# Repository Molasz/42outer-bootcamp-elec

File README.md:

# Bootcamp Electronics - 42 Paris

_This project has been created as part of the 42 curriculum by molasz-a._

> Part of [42 Barcelona — molasz-a](https://github.com/Molasz/42), a monorepo centralizing every project completed at 42 Barcelona.

## Description

This repository contains the schematic, PCB layout and custom symbol and footprint for each component for a custom-designed microcontroller board based on the **ATmega328P**. The board was designed using KiCad 9.0.

## Bill of Materials (BOM)

| Reference | Qty | Name | Footprint | Description |
| :--- | :---: | :--- | :--- | :--- |
| **U1** | 1 | ATmega328P-AU | TQFP-32_7x7mm_P0.8mm | 8-bit AVR Microcontroller |
| **Y1** | 1 | 16.000 MHz | Crystal_SMD_3225-4Pin | SMD Quartz Crystal (3.2x2.5mm) |
| **C1, C2** | 2 | 12pF | C_0805_2012Metric | Ceramic Load Capacitors for Y1 |
| **C3, C4, C7**| 3 | 100nF | C_0805_2012Metric | Decoupling & DTR Capacitors |
| **C6**| 1 | 1uF | C_0805_2012Metric | Decoupling |
| **R1** | 1 | 330Ω | R_0805_2012Metric | Current limiting resistor for D1 |
| **R2, R3** | 2 | 10kΩ | R_0805_2012Metric | Current limiting resistor for D2 & pull-up resistor for reset line |
| **D1, D2** | 2 | LED | LED_0805_2012Metric | Status LEDs (Red/Green) |
| **SW1** | 1 | Tactile Switch | SW_Tact_6X6mm_H5mm_SMD | Reset Button |
| **J1, J2** | 2 | 1x12 Header | PinHeader_1x12_P2.54mm | Vertical Through-Hole Header |
| **J3** | 1 | 1x06 Header | PinHeader_1x06_P2.54mm | FTDI Programming Header |

---

## Pinout Diagram

### J1
| Pin | Label | Function |
| :---: | :--- | :--- |
| **1** | D9 | Digital Pin 9 (PWM) |
| **2** | D8 | Digital Pin 8 |
| **3** | D7 | Digital Pin 7 |
| **4** | D6 | Digital Pin 6 (PWM) |
| **5** | D5 | Digital Pin 5 (PWM) |
| **6** | D4 | Digital Pin 4 |
| **7** | D3 | Digital Pin 3 (PWM) |
| **8** | D2 | Digital Pin 2 |
| **9** | GND | Ground |
| **10** | DTR | Reset / DTR |
| **11** | RXI | Digital Pin 0 / RX |
| **12** | TXO | Digital Pin 1 / TX |

### J2
| Pin | Label | Function |
| :---: | :--- | :--- |
| **1** | RAW | Power Input |
| **2** | GND | Ground |
| **3** | RST | Reset |
| **4** | VCC | Power Input |
| **5** | A3 | Analog Input 3 |
| **6** | A2 | Analog Input 2 |
| **7** | A1 | Analog Input 1 |
| **8** | A0 | Analog Input 0 |
| **9** | SCK | Digital Pin 13 / SPI Clock |
| **10**| MISO| Digital Pin 12 / SPI MISO |
| **11**| MOSI| Digital Pin 11 / SPI MOSI (PWM) |
| **12**| D10 | Digital Pin 10 (PWM) / SPI SS |

### J3 - FTDI
Standard 6-pin interface used to program the ATmega328P via a USB-to-Serial adapter.
| Pin | Label | Function |
| :---: | :--- | :--- |
| **1** | DTR | Auto-Reset |
| **2** | TXO | Serial Transmit |
| **3** | RXI | Serial Receive |
| **4** | VCC | Power Input |
| **5** | GND | Ground |
| **6** | GND | Ground |

---

## Schema

## PCB design

</br>

---

_molasz-a · 42 Paris_

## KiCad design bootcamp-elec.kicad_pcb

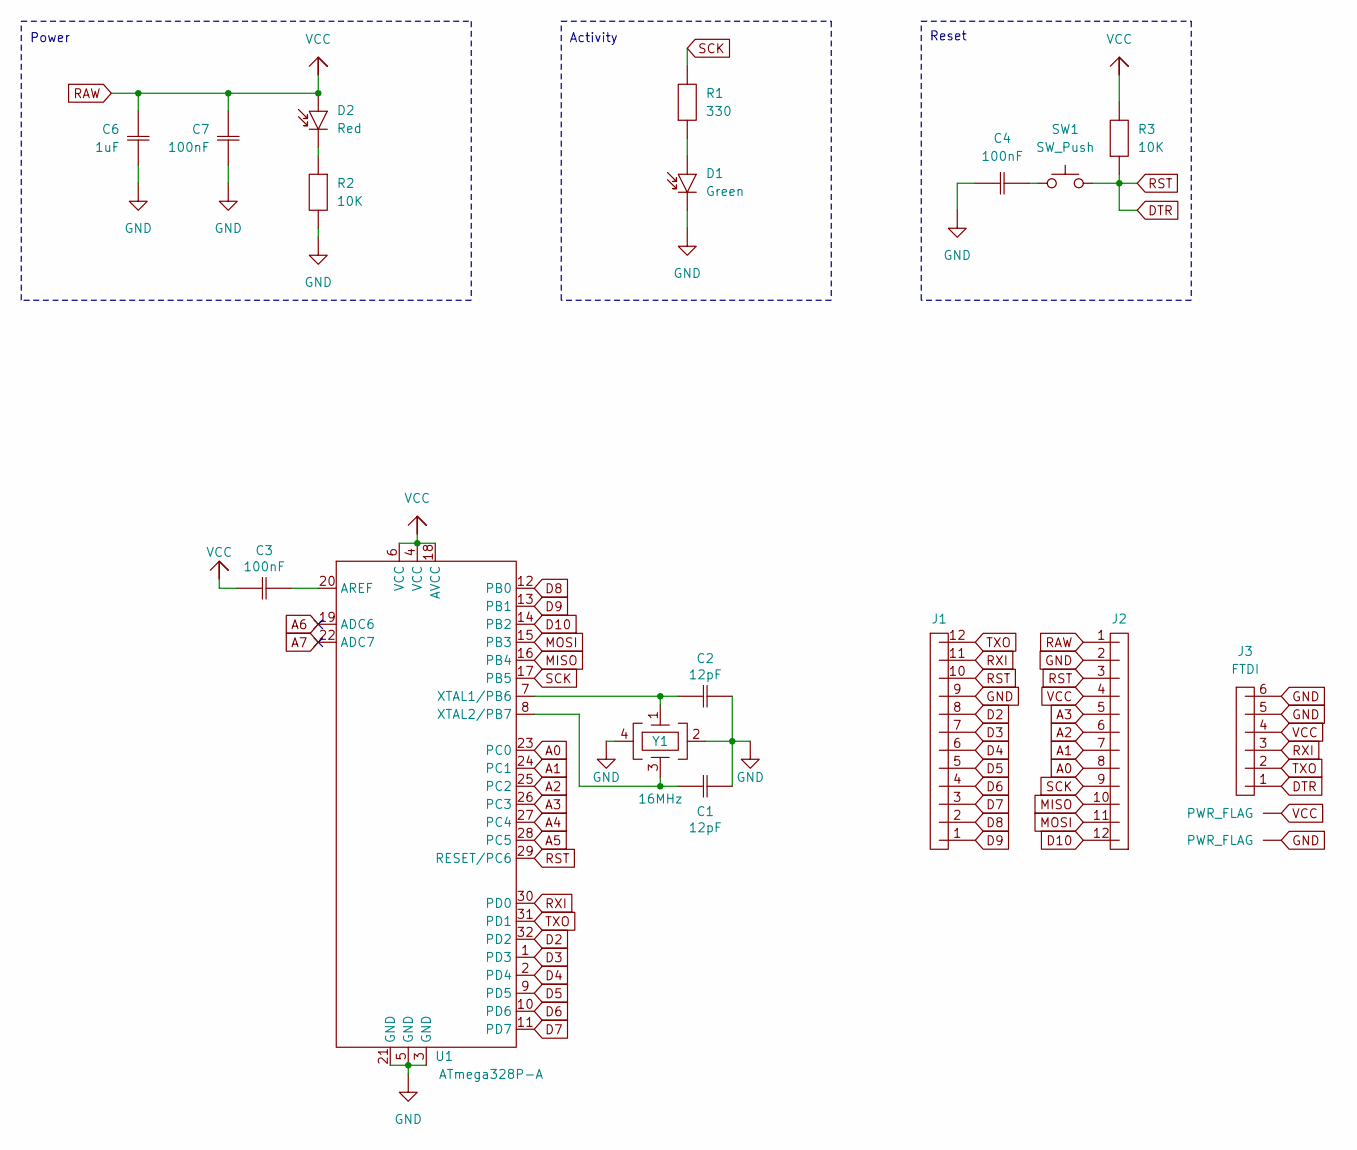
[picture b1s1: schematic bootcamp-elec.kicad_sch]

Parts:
C1, C2: 12pF; C_0805_2012Metric
C3, C4, C7: 100nF; C_0805_2012Metric
C6: 1uF; C_0805_2012Metric
D1: Green; LED_0805_2012Metric
D2: Red; LED_0805_2012Metric
J1, J2: PinHeader_1x12_P2.54mm_Vertical
J3: FTDI; PinHeader_1x06_P2.54mm_Vertical
R1: 330; R_0805_2012Metric
R2, R3: 10K; R_0805_2012Metric
SW1: SW_Push; SW_Tact_6X6mm_H5mm_SMD
U1: ATmega328P-A; TQFP-32_7x7mm_P0.8mm
Y1: 16MHz; Crystal_SMD_3225-4Pin_3.2x2.5mm

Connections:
A0: J2.8, U1.23 (PC0)
A1: J2.7, U1.24 (PC1)
A2: J2.6, U1.25 (PC2)
A3: J2.5, U1.26 (PC3)
A4: U1.27 (PC4)
A5: U1.28 (PC5)
A6: U1.19 (ADC6)
A7: U1.22 (ADC7)
D2: J1.8, U1.32 (PD2)
D3: J1.7, U1.1 (PD3)
D4: J1.6, U1.2 (PD4)
D5: J1.5, U1.9 (PD5)
D6: J1.4, U1.10 (PD6)
D7: J1.3, U1.11 (PD7)
D8: J1.2, U1.12 (PB0)
D9: J1.1, U1.13 (PB1)
D10: J2.12, U1.14 (PB2)
DTR: J1.10, J2.3, J3.1, R3.1, SW1.2, U1.29 (RESET/PC6)
MISO: J2.10, U1.16 (PB4)
MOSI: J2.11, U1.15 (PB3)
unnamed: C4.1, SW1.1
unnamed: D1.2, R1.1
unnamed: D2.1, R2.1
unnamed: C3.2, U1.20 (AREF)
unnamed: C2.1, U1.7 (XTAL1/PB6), Y1.1
unnamed: C1.1, U1.8 (XTAL2/PB7), Y1.3
RXI: J1.11, J3.3, U1.30 (PD0)
SCK: J2.9, R1.2, U1.17 (PB5)
TXO: J1.12, J3.2, U1.31 (PD1)

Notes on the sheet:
Power
Activity
Reset

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
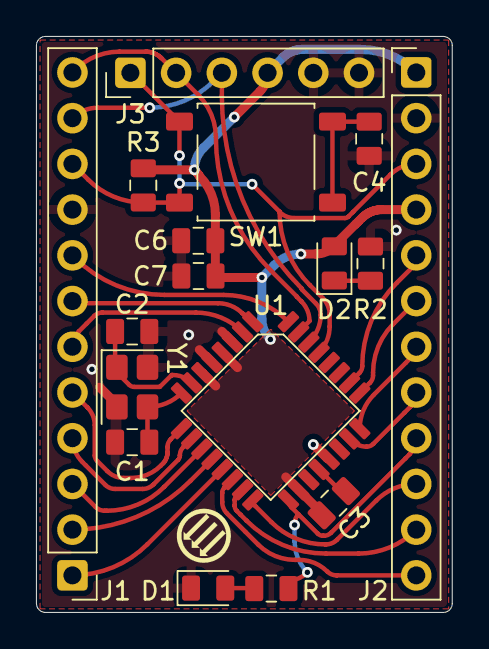
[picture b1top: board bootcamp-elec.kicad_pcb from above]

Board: 2 copper layers, 23.1 x 32.0 mm, 17 parts (0 on the bottom side), 27 nets.

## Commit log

2026-05-11 firsts symbols
2026-05-11 symbols library done
2026-05-11 create schema & adapt sym
2026-05-11 ERC no errors
2026-05-12 fix refs
2026-05-12 create footprint lib
2026-05-13 footprints done
2026-05-13 add silkscreen logo & pcb config
2026-05-13 pcb design done
2026-05-14 resolve DRC errors/warns
2026-05-14 add tear drops
2026-05-14 add Drill/Place File Origin
2026-05-14 add pdfs
2026-05-14 add readme
2026-05-14 fix img
2026-05-14 add table
2026-05-14 use p tag
2026-05-14 update img
2026-05-14 adjust readme texts
2026-05-14 resize img
2026-05-14 readme fixes
2026-05-15 redesign pcb
2026-05-15 pcb design v3
2026-05-15 update assets
2026-05-15 update pcb_design export
2026-05-16 move footprints
2026-05-16 pcb_design 4.0
